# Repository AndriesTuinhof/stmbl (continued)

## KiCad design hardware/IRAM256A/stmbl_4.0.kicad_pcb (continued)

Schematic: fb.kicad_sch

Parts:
C13, C36, C72, C74, C75, C113, C114, C115, C125: 100n; C_0603; Voltage 50V; Tolerance X5R
C25, C27: 18p; C_0603; Voltage 50V; Tolerance X5R
C47, C48: 1n; C_0603; Voltage 50V; Tolerance X5R
J2: RJ45_LED
JP2: JUMPER3_NC; SOLDER_JUMPER_3_NC
L8, L9: 220r 700mA; R_0603
R3, R6, R93, R95: 470; R_0603; Tolerance 1%
R24, R25, R109, R111, R114, R130: 120; R_0603; Tolerance 1%
R36, R39, R42, R44, R135, R137: 10k; R_0603; Tolerance 1%
R47, R50, R55, R56: 15k; R_0603; Tolerance 1%
R86, R89, R147: 22; R_0603; Tolerance 1%
R123, R125, R128, R136: 1k; R_0603; Tolerance 1%
U6: LM358; SOIC-8-N
U14, U17, U18: SN65176B; SO-8

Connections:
+5F: C115.2, JP2.1, L9.1, R137.2; also elsewhere on the board
+5VA: C113.2, L8.1; also elsewhere on the board
+12V: JP2.3; also elsewhere on the board
/ctrl/FB0/A12: C47.1, R86.1, R93.1; also elsewhere on the board
/ctrl/FB0/A35: C48.1, R89.1, R95.1; also elsewhere on the board
/ctrl/FB0/A78: C125.1, R135.2, R136.1; also elsewhere on the board
/ctrl/FB0/D12: U14.1 (RO), U14.4 (DI); also elsewhere on the board
/ctrl/FB0/D36: U17.1 (RO), U17.4 (DI); also elsewhere on the board
/ctrl/FB0/D45: U18.1 (RO), U18.4 (DI); also elsewhere on the board
/ctrl/FB0/E12: R123.1, U14.2 (~RE), U14.3 (DE); also elsewhere on the board
/ctrl/FB0/E36: R125.1, U17.2 (~RE), U17.3 (DE); also elsewhere on the board
/ctrl/FB0/E45: R128.1, U18.2 (~RE), U18.3 (DE); also elsewhere on the board
/ctrl/FB0/L1: J2.12; also elsewhere on the board
/ctrl/FB0/L2: J2.10; also elsewhere on the board
GND: C13.2, C36.1, C47.2, C48.2, C72.2, C74.2, C75.2, C113.1, C114.2, C115.1, C125.2, J2.8, R3.2, R6.2, R25.2, R93.2, R95.2, R123.2, R125.2, R128.2, R136.2, U6.4 (V-), U14.5 (GND), U17.5 (GND), U18.5 (GND); also elsewhere on the board
GNDD: J2.13; also elsewhere on the board
unnamed: C13.1, R24.2, R47.1, R50.1, R147.1
unnamed: C25.1, R36.1, R50.2, U6.5 (+)
unnamed: C25.2, R39.1, R56.2, U6.6 (-)
unnamed: C27.1, R42.1, R47.2, U6.3 (+)
unnamed: C27.2, R44.1, R55.2, U6.2 (-)
unnamed: C36.2, L8.2, R130.1, U6.8 (V+)
unnamed: C72.1, C74.1, C75.1, L9.2, U14.8 (VCC), U17.8 (VCC), U18.8 (VCC)
unnamed: C114.1, J2.7, JP2.2, R135.1, R137.1
unnamed: J2.1, R42.2, R109.1, U14.6 (A)
unnamed: J2.2, R44.2, R109.2, U14.7 (B)
unnamed: J2.3, R36.2, R111.1, U17.6 (A)
unnamed: J2.4, R114.2, U18.7 (B)
unnamed: J2.5, R114.1, U18.6 (A)
unnamed: J2.6, R39.2, R111.2, U17.7 (B)
unnamed: J2.9, R6.1
unnamed: J2.11, R3.1
unnamed: R55.1, R86.2, U6.1
unnamed: R56.1, R89.2, U6.7
unnamed: R24.1, R130.2
unnamed: R25.1, R147.2

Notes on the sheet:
4.94V / (120 + 120 + 120 + 22) * (120 + 22) = 1.83V
LM358 max. output: 4.94V - 1.5V = 3.44V STM32 max. input: 3.44V / (22 + 470) * 470 = 3.28V

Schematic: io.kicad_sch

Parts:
C52, C59: 1n; C_0603; Voltage 50V; Tolerance X5R
C91, C94, C95, C98, C100, C130: 100n; C_0603; Voltage 50V; Tolerance X5R
D2, D3, D5, D7: ES1J R2; SMA_Standard
D4, D14, D15, D18, D19, D20: green; LED-0805-SIDE
D16: red; LED-0805-SIDE
D17: yellow; LED-0805-SIDE
JP3: JUMPER3_NC; SOLDER_JUMPER_3_NC
P4: CONN_01X02; Pin_Header_Angled_1x02
P5, P9: CONN_01X06; RM3.5_1x6
P10: CONN_02X06; Socket_Strip_Angled_2x06
Q1, Q2, Q3, Q4: IRLML6344; SOT-23
R9, R10, R11, R40: 22; R_0603; Tolerance 1%
R12, R13, R14, R45, R99, R105, R108, R119: 1k; R_0603; Tolerance 1%
R20, R22, R74: 3.9k; R_0603; Tolerance 1%
R76, R83, R85, R120, R134: 470; R_0603; Tolerance 1%
R98, R106: 10k; R_0603; Tolerance 1%

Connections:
+3V3: R105.1, R119.1; also elsewhere on the board
+5V: P10.12; also elsewhere on the board
+12V: JP3.1; also elsewhere on the board
+24V: C91.1, C94.1, C95.1, C100.1, C130.1, D2.1 (K), D3.1 (K), D4.2 (A), D5.1 (K), D14.2 (A), D15.2 (A), JP3.3, P5.1, P5.3, P5.5, P9.1, P9.4, P10.11; also elsewhere on the board
/ctrl/CMD/D12: P10.3; also elsewhere on the board
/ctrl/CMD/D36: P10.2; also elsewhere on the board
/ctrl/CMD/D45: P10.1; also elsewhere on the board
/ctrl/IO/CAN_RX: P10.7; also elsewhere on the board
/ctrl/IO/CAN_TX: P10.5; also elsewhere on the board
/ctrl/IO/IO_FAN: R40.2; also elsewhere on the board
/ctrl/IO/IO_GREEN: D18.2 (A); also elsewhere on the board
/ctrl/IO/IO_IN0: C52.1, R98.2, R99.1, R105.2; also elsewhere on the board
/ctrl/IO/IO_IN1: C59.1, R106.2, R108.1, R119.2; also elsewhere on the board
/ctrl/IO/IO_L0: D19.2 (A); also elsewhere on the board
/ctrl/IO/IO_L1: D20.2 (A); also elsewhere on the board
/ctrl/IO/IO_OUT0: R11.2; also elsewhere on the board
/ctrl/IO/IO_OUT1: R10.2; also elsewhere on the board
/ctrl/IO/IO_OUT2: R9.2; also elsewhere on the board
/ctrl/IO/IO_RED: D16.2 (A); also elsewhere on the board
/ctrl/IO/IO_YELLOW: D17.2 (A); also elsewhere on the board
/ctrl/IO/NRST: P10.4; also elsewhere on the board
/ctrl/IO/SWCK: P10.10; also elsewhere on the board
/ctrl/IO/SWDIO: P10.6; also elsewhere on the board
GND: C52.2, C59.2, C91.2, C94.2, C95.2, C98.2, C100.2, C130.2, P9.3, P9.6, P10.8, P10.9, Q1.2 (S), Q2.2 (S), Q3.2 (S), Q4.2 (S), R12.2, R13.2, R14.2, R45.2, R76.2, R83.2, R85.2, R99.2, R108.2, R120.2, R134.2; also elsewhere on the board
unnamed: C98.1, D7.1 (K), JP3.2, P4.2
unnamed: D2.2 (A), P5.2, Q1.3 (D), R20.2
unnamed: D3.2 (A), P5.4, Q2.3 (D), R22.2
unnamed: D4.1 (K), R20.1
unnamed: D5.2 (A), P5.6, Q3.3 (D), R74.2
unnamed: D7.2 (A), P4.1, Q4.3 (D)
unnamed: D14.1 (K), R22.1
unnamed: D15.1 (K), R74.1
unnamed: D16.1 (K), R76.1
unnamed: D17.1 (K), R83.1
unnamed: D18.1 (K), R85.1
unnamed: D19.1 (K), R120.1
unnamed: D20.1 (K), R134.1
unnamed: P9.2, R98.1
unnamed: P9.5, R106.1
unnamed: Q1.1 (G), R9.1, R12.1
unnamed: Q2.1 (G), R10.1, R13.1
unnamed: Q3.1 (G), R11.1, R14.1
unnamed: Q4.1 (G), R40.1, R45.1

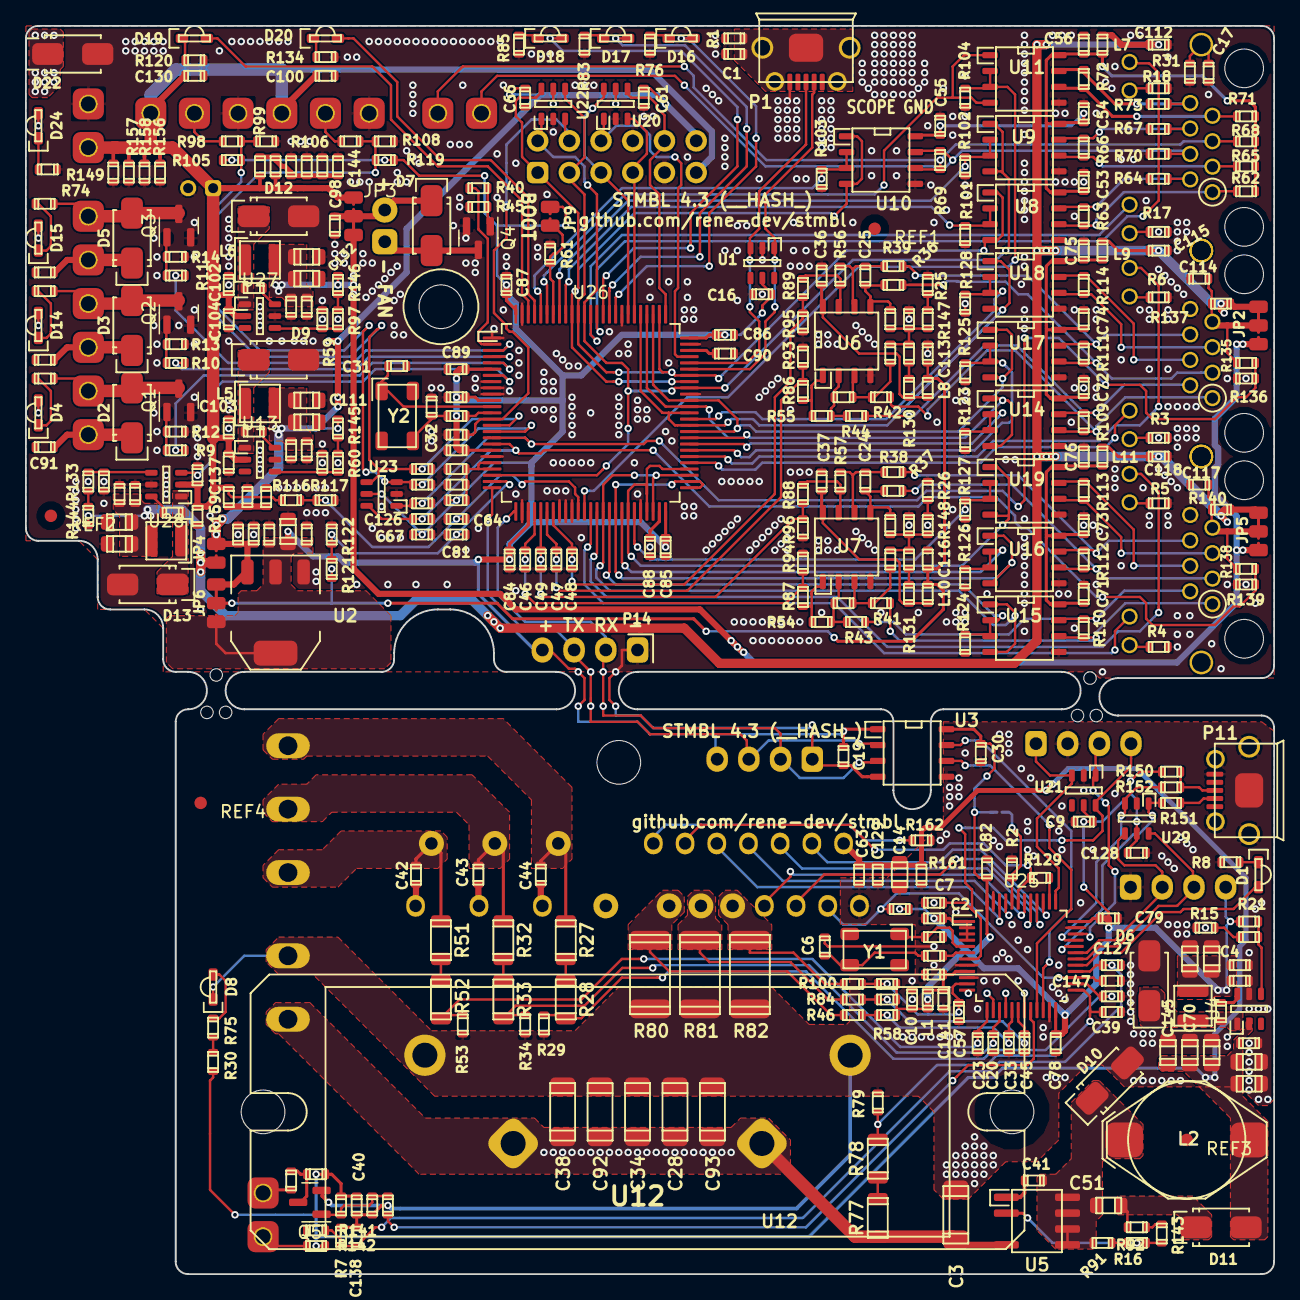
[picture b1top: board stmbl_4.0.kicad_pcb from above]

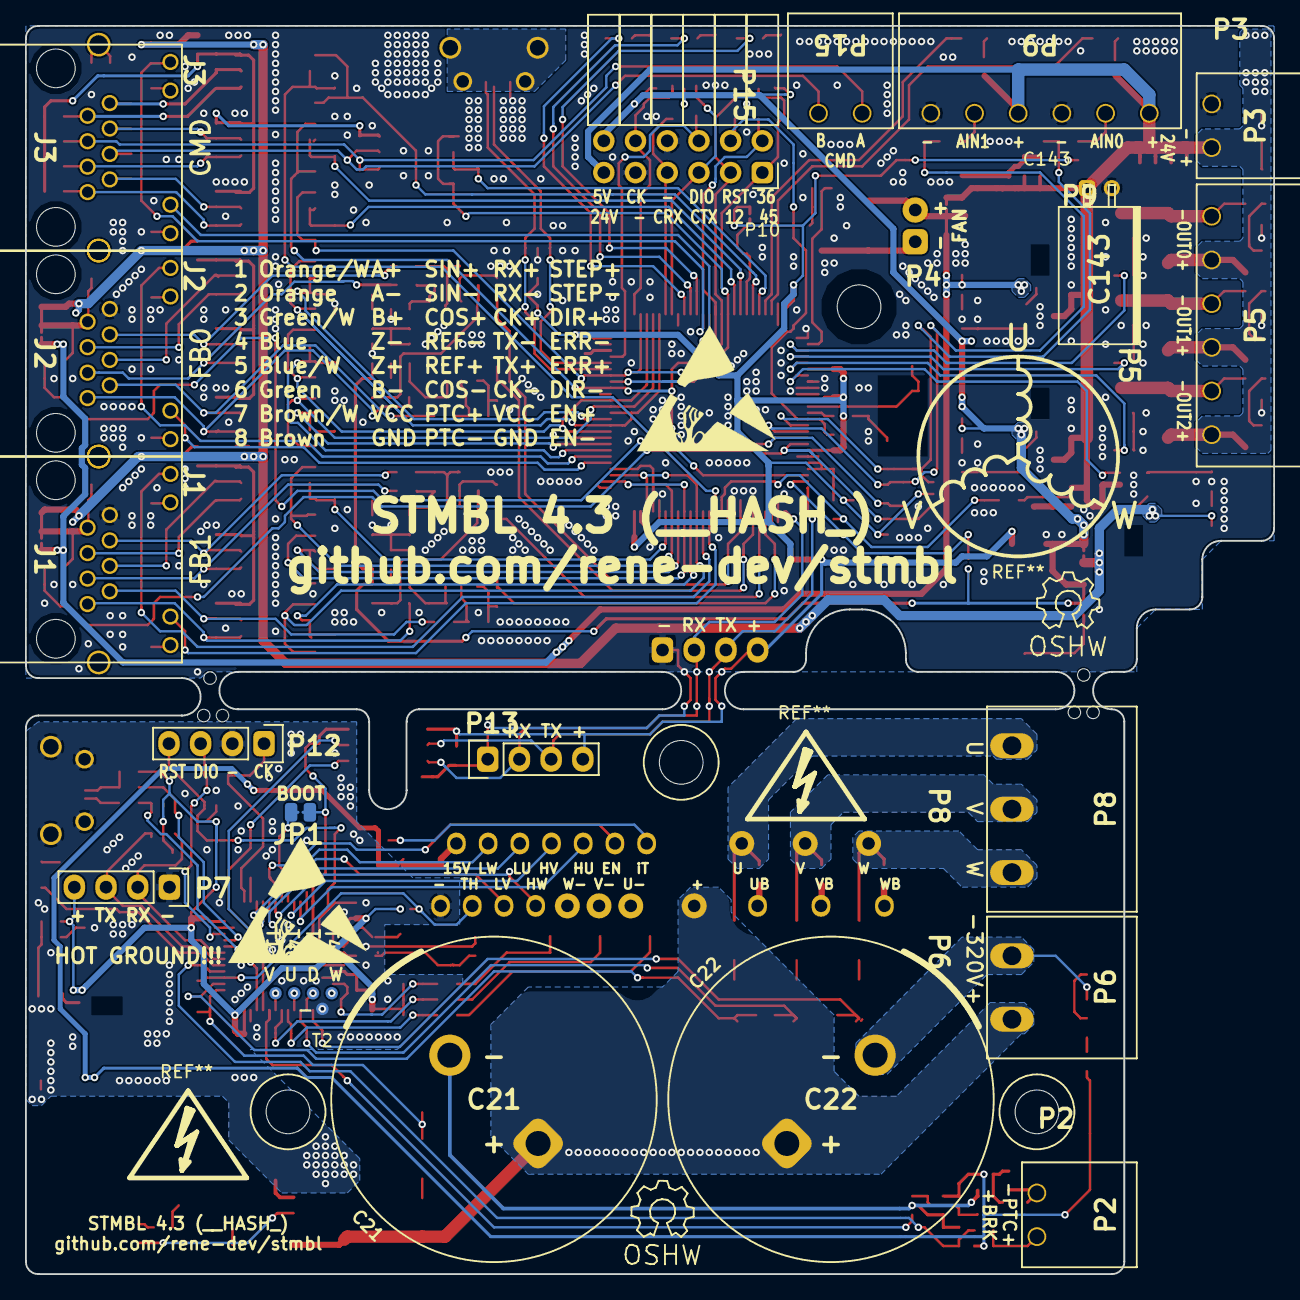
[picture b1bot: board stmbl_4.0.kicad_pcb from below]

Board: 2 copper layers, 100.0 x 100.0 mm, 428 parts (29 on the bottom side), 230 nets.

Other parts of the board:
C12, C37, C71, C73, C76, C116, C117, C118, C126: 100n; C_0603
C24, C26: 18p; C_0603
C46, C49: 1n; C_0603
J1: RJ45_LED
JP5: JUMPER3_NC; SOLDER_JUMPER_3_NC
L10, L11: 220r 700mA; R_0603
LOGO1#2: OPEN_HARDWARE_1; Symbol_OSHW-Logo_SilkScreen
R4, R5, R94, R96: 470; R_0603
R23, R26, R110, R112, R113, R131: 120; R_0603
R37, R38, R41, R43, R138, R140: 10k; R_0603
R48, R49, R54, R57: 15k; R_0603
R87, R88, R148: 22; R_0603
R124, R126, R127, R139: 1k; R_0603
REF1, REF2, REF3, REF4: Fiducial_1mm_Dia_2.54mm_Outer_CopperTop; Fiducial_1mm_Outer_CopperTop
U7: LM358; SOIC-8-N
U15, U16, U19: SN65176B; SOIC-8-N
U35, U36, U37, U39: non_plated; non_plated_1mm

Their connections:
+5F: C118.2, JP5.1, L11.1, R140.2; also elsewhere on the board
+5VA: C116.2, L10.1; also elsewhere on the board
+12V: JP5.3; also elsewhere on the board
/ctrl/FB1/A12: C46.1, R87.1, R94.1; also elsewhere on the board
/ctrl/FB1/A35: C49.1, R88.1, R96.1; also elsewhere on the board
/ctrl/FB1/A78: C126.1, R138.2, R139.1; also elsewhere on the board
/ctrl/FB1/D12: U15.1 (RO), U15.4 (DI); also elsewhere on the board
/ctrl/FB1/D36: U16.1 (RO), U16.4 (DI); also elsewhere on the board
/ctrl/FB1/D45: U19.1 (RO), U19.4 (DI); also elsewhere on the board
/ctrl/FB1/E12: R124.1, U15.2 (~RE), U15.3 (DE); also elsewhere on the board
/ctrl/FB1/E36: R126.1, U16.2 (~RE), U16.3 (DE); also elsewhere on the board
/ctrl/FB1/E45: R127.1, U19.2 (~RE), U19.3 (DE); also elsewhere on the board
/ctrl/FB1/L1: J1.12; also elsewhere on the board
/ctrl/FB1/L2: J1.10; also elsewhere on the board
GND: C12.2, C37.1, C46.2, C49.2, C71.2, C73.2, C76.2, C116.1, C117.2, C118.1, C126.2, J1.8, R4.2, R5.2, R26.2, R94.2, R96.2, R124.2, R126.2, R127.2, R139.2, U7.4 (V-), U15.5 (GND), U16.5 (GND), U19.5 (GND); also elsewhere on the board
GNDD: J1.13; also elsewhere on the board
unnamed: C12.1, R23.2, R48.1, R49.1, R148.1
unnamed: C24.1, R37.1, R49.2, U7.5 (+)
unnamed: C24.2, R38.1, R57.2, U7.6 (-)
unnamed: C26.1, R41.1, R48.2, U7.3 (+)
unnamed: C26.2, R43.1, R54.2, U7.2 (-)
unnamed: C37.2, L10.2, R131.1, U7.8 (V+)
unnamed: C71.1, C73.1, C76.1, L11.2, U15.8 (VCC), U16.8 (VCC), U19.8 (VCC)
unnamed: C117.1, J1.7, JP5.2, R138.1, R140.1
unnamed: J1.1, R41.2, R110.1, U15.6 (A)
unnamed: J1.2, R43.2, R110.2, U15.7 (B)
unnamed: J1.3, R37.2, R112.1, U16.6 (A)
unnamed: J1.4, R113.2, U19.7 (B)
unnamed: J1.5, R113.1, U19.6 (A)
unnamed: J1.6, R38.2, R112.2, U16.7 (B)
unnamed: J1.9, R5.1
unnamed: J1.11, R4.1
unnamed: R54.1, R87.2, U7.1
unnamed: R57.1, R88.2, U7.7
unnamed: R23.1, R131.2
unnamed: R26.1, R148.2

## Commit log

2022-10-24 file structure change
2022-10-24 file structure change + kicad update
2022-10-24 Structure change + kicad 3d models updated
2022-10-29 moved git ignore back + added some ignores
2022-10-29 Update some package (3D models) + replaced ACT4088 with AOZ1280
    AOZ1280 is quite similar to the act4088 with the benefit of being still available for a reasonable price. with the drawback of pinout being different. The schematic had to be moved around and is no l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
2022-10-29 Added pin header & cap 3d model
2023-01-08 intermediate update
